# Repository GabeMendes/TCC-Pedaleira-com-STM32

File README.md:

# TCC-Pedaleira-com-STM32
Desenvolvimento de Unidade de Efeitos de áudio (Pedaleira) para Guitarra destinado ao Estudo de Processamento Digital de Sinais.

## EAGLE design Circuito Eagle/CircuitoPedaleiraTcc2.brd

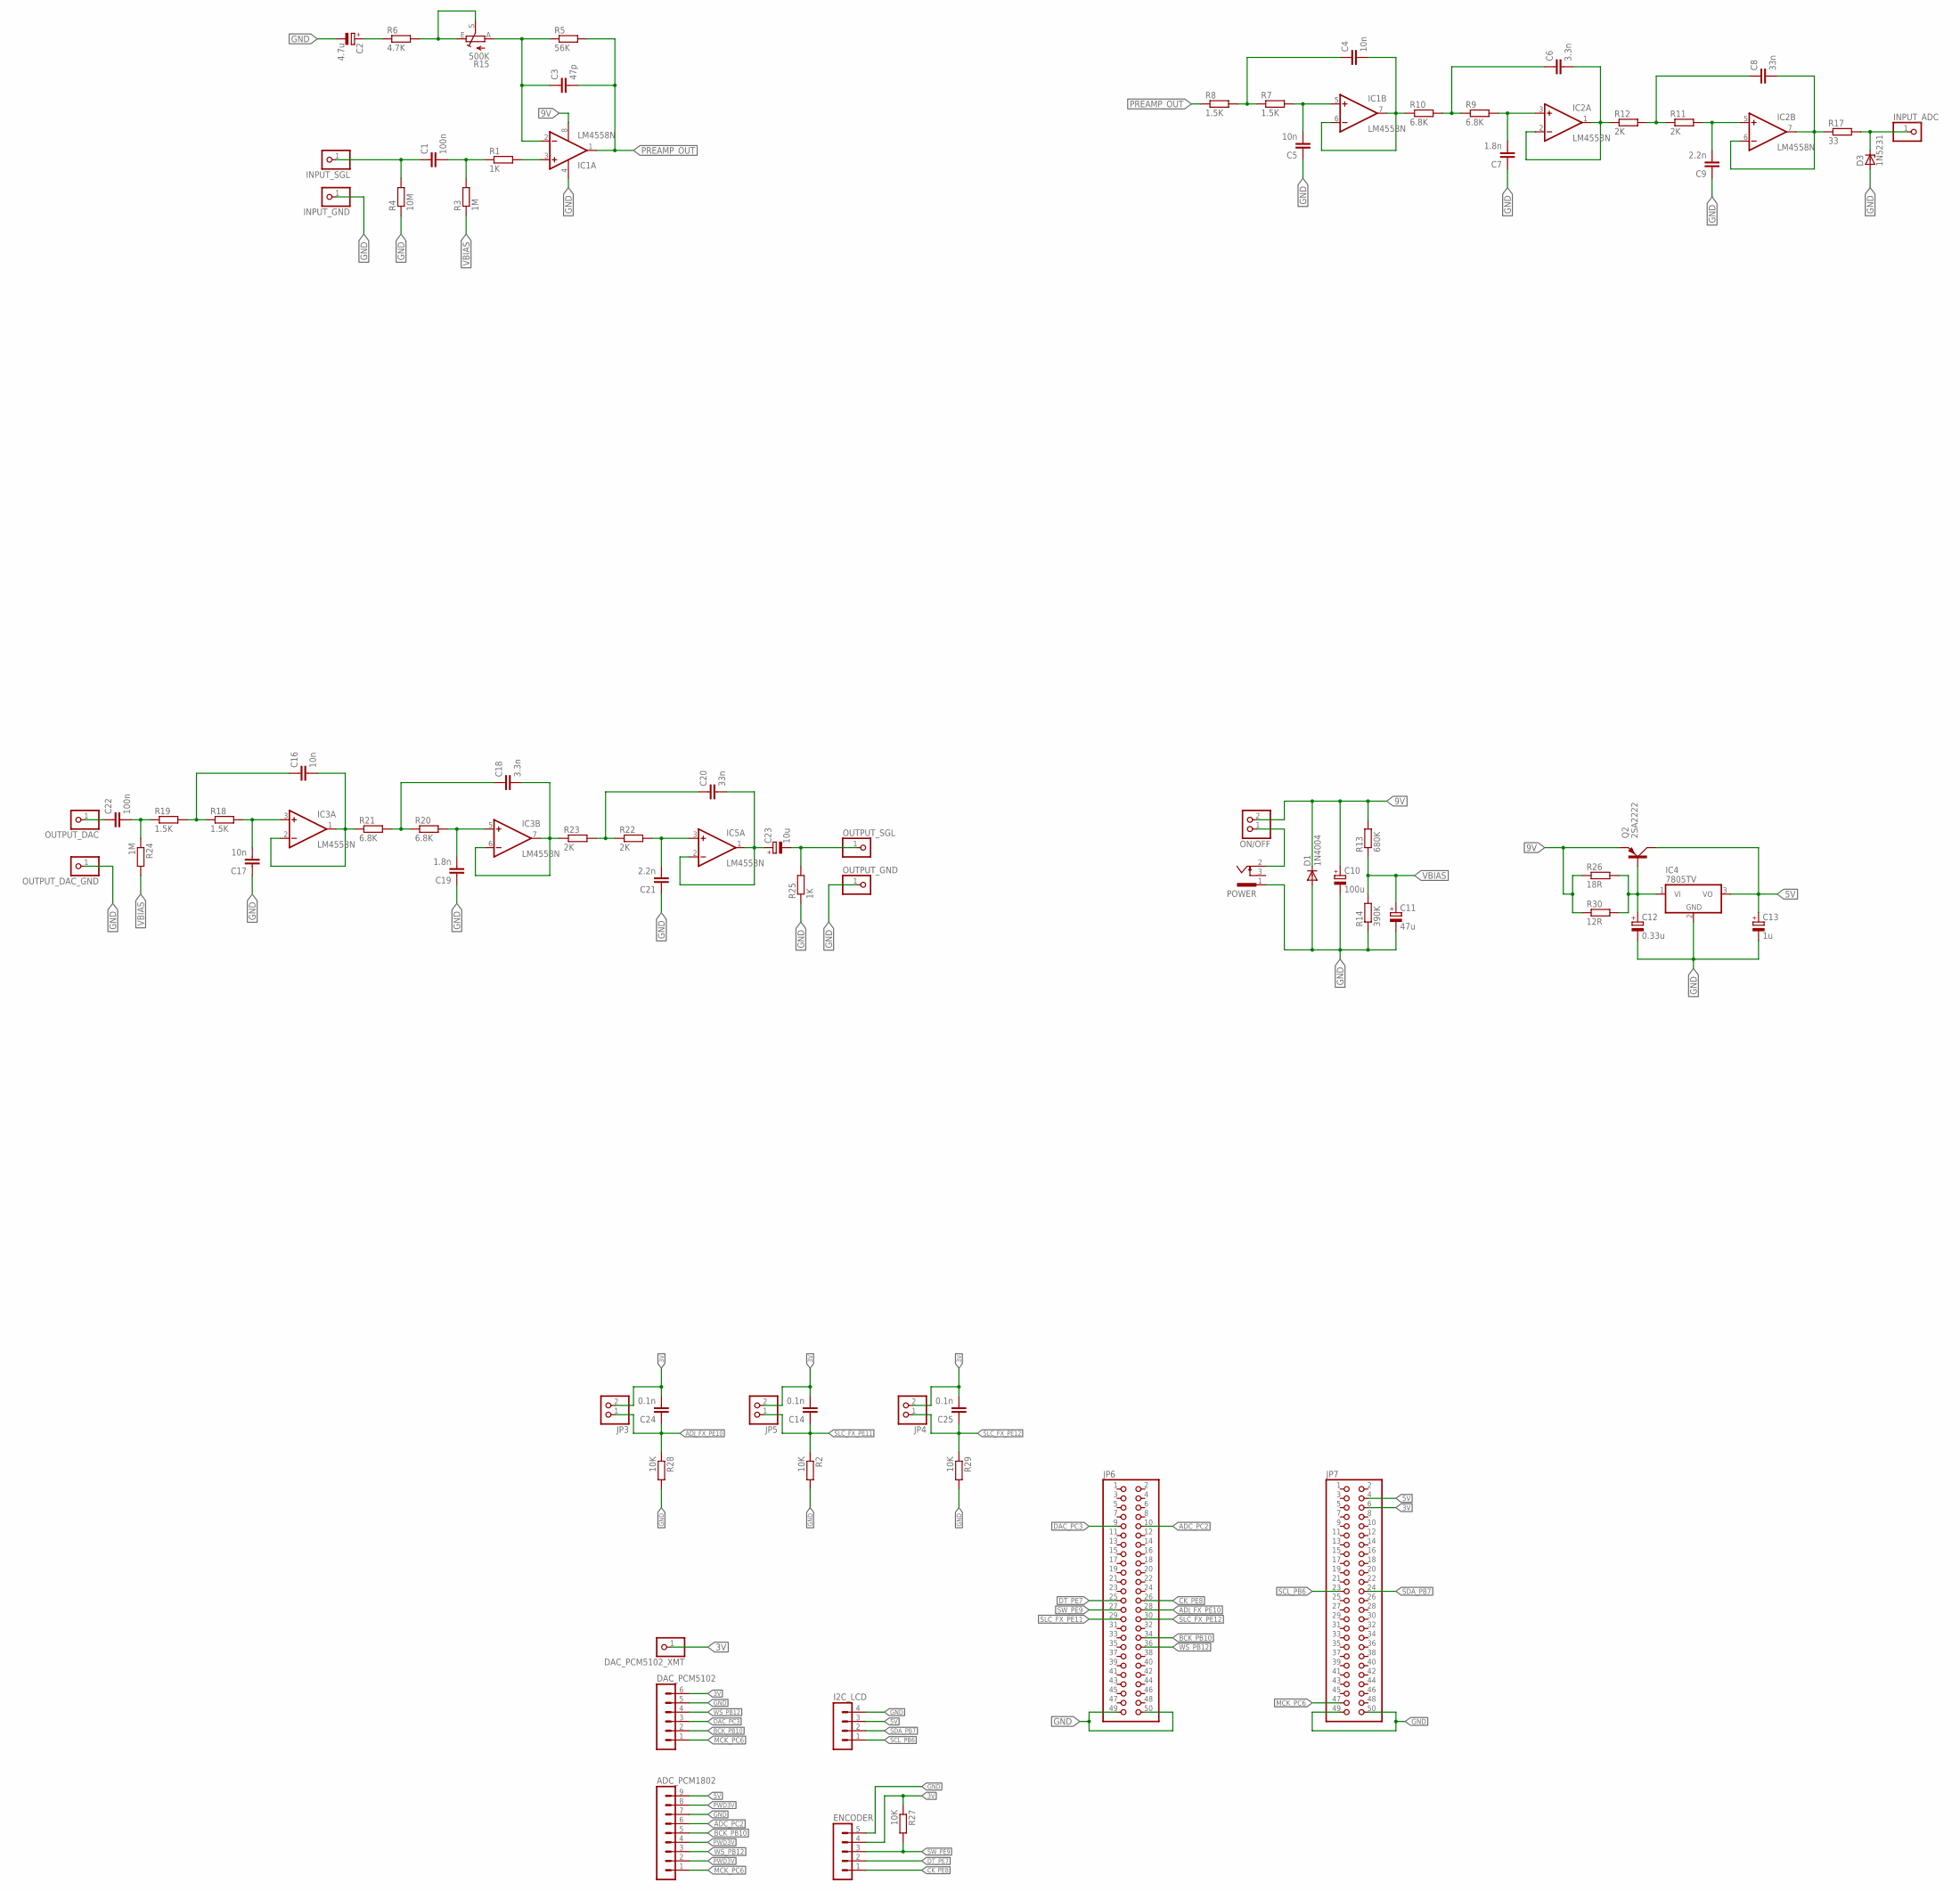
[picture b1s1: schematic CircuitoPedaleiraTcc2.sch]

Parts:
ADC_PCM1802: MA09-1
C1, C22: 100n; C025-025X050
C2: 4.7u; E2,5-6
C3: 47p; C025-025X050
C4, C5, C16, C17: 10n; C025-025X050
C6, C18: 3.3n; C025-025X050
C7, C19: 1.8n; C025-025X050
C8, C20: 33n; C025-025X050
C9, C21: 2.2n; C025-025X050
C10: 100u; E2,5-6
C11: 47u; E2,5-6
C12: 0.33u; E2,5-6
C13: 1u; E2,5-6
C14, C24, C25: 0.1n; C025-025X050
C23: 10u; E2,5-6
D1: 1N4004; DO41-10
D3: 1N5231; DO35Z10
DAC_PCM5102: MA06-1
DAC_PCM5102_XMT: PINHD-1X1; 1X01
ENCODER: MA05-1
I2C_LCD: MA04-1
IC1, IC2, IC3, IC5: LM4558N; DIL08
IC4: 7805TV; TO220V
INPUT_ADC: PINHD-1X1; 1X01
INPUT_GND: PINHD-1X1; 1X01
INPUT_SGL: PINHD-1X1; 1X01
JP3, JP4, JP5: PINHD-1X2; 1X02
JP6, JP7: PINHD-2X25; 2X25
ON/OFF: PINHD-1X2; 1X02
OUTPUT_DAC: PINHD-1X1; 1X01
OUTPUT_DAC_GND: PINHD-1X1; 1X01
OUTPUT_GND: PINHD-1X1; 1X01
OUTPUT_SGL: PINHD-1X1; 1X01
POWER: SCD-014A; SCD-014-A
Q2: 2SA2222; TO220AV
R1, R25: 1K; 0204/7
R2, R27, R28, R29: 10K; 0204/7
R3, R24: 1M; 0204/7
R4: 10M; 0204/7
R5: 56K; 0204/7
R6: 4.7K; 0204/7
R7, R8, R18, R19: 1.5K; 0204/7
R9, R10, R20, R21: 6.8K; 0204/7
R11, R12, R22, R23: 2K; 0204/7
R13: 680K; 0204/7
R14: 390K; 0204/7
R15: 500K; B25X
R17: 33; 0204/7
R26: 18R; 0411/15
R30: 12R; 0411/15

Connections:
3V: C14.2, C24.2, C25.2, DAC_PCM5102.6, DAC_PCM5102_XMT.1, ENCODER.4, JP3.2, JP4.2, JP5.2, JP7.6, R27.1
5V: ADC_PCM1802.9, C13.+, I2C_LCD.3, IC4.3 (VO), JP7.4, Q2.C
9V: C10.+, D1.C, IC1.8 (V+), ON/OFF.2, Q2.E, R13.2, R26.1, R30.1
ADC_PC2: ADC_PCM1802.6, JP6.10
ADJ_FX_PE10: C24.1, JP3.1, JP6.28, R28.1
AL_LP_OUT: C8.2, IC2.6 (-IN), IC2.7 (OUT), R17.1
AL_LP_OUT1: C20.2, C23.+, IC5.1 (OUT), IC5.2 (-IN)
BCK_PB10: ADC_PCM1802.5, DAC_PCM5102.2, JP6.34
CK_PE8: ENCODER.1, JP6.26
DAC_PC3: DAC_PCM5102.3, JP6.9
DT_PE7: ENCODER.2, JP6.25
GND: ADC_PCM1802.7, C2.-, C5.1, C7.1, C9.1, C10.-, C11.-, C12.-, C13.-, C17.1, C19.1, C21.1, D1.A, D3.A, DAC_PCM5102.5, ENCODER.5, I2C_LCD.4, IC1.4 (V-), IC4.2 (GND), INPUT_GND.1, JP6.49, JP6.50, JP7.49, JP7.50, OUTPUT_DAC_GND.1, OUTPUT_GND.1, POWER.1, R2.2, R4.1, R14.1, R25.1, R28.2, R29.2
INPUT: C1.1, INPUT_SGL.1, R4.2
INPUT_ADC: D3.C, INPUT_ADC.1, R17.2
MCK_PC6: ADC_PCM1802.1, DAC_PCM5102.1, JP7.47
unnamed: IC1.3 (+IN), R1.2
unnamed: C1.2, R1.1, R3.2
unnamed: ON/OFF.1, POWER.2
unnamed: C3.1, IC1.2 (-IN), R5.1, R15.A
unnamed: C4.2, IC1.6 (-IN), IC1.7 (OUT), R10.1
unnamed: R6.2, R15.E, R15.S
unnamed: C2.+, R6.1
unnamed: C16.2, IC3.1 (OUT), IC3.2 (-IN), R21.1
unnamed: C5.2, IC1.5 (+IN), R7.2
unnamed: C4.1, R7.1, R8.2
unnamed: C6.2, IC2.1 (OUT), IC2.2 (-IN), R12.1
unnamed: C7.2, IC2.3 (+IN), R9.2
unnamed: C6.1, R9.1, R10.2
unnamed: C9.2, IC2.5 (+IN), R11.2
unnamed: C8.1, R11.1, R12.2
unnamed: C17.2, IC3.3 (+IN), R18.2
unnamed: C16.1, R18.1, R19.2
unnamed: C18.2, IC3.6 (-IN), IC3.7 (OUT), R23.1
unnamed: C19.2, IC3.5 (+IN), R20.2
unnamed: C18.1, R20.1, R21.2
unnamed: C21.2, IC5.3 (+IN), R22.2
unnamed: C20.1, R22.1, R23.2
unnamed: C22.2, R19.1, R24.1
unnamed: C22.1, OUTPUT_DAC.1
unnamed: C12.+, IC4.1 (VI), Q2.B, R26.2, R30.2
OUTPUT: C23.-, OUTPUT_SGL.1, R25.2
PREAMP_OUT: C3.2, IC1.1 (OUT), R5.2, R8.1
PWD3V: ADC_PCM1802.2, ADC_PCM1802.4, ADC_PCM1802.8
SCL_PB6: I2C_LCD.1, JP7.23
SDA_PB7: I2C_LCD.2, JP7.24
SLC_FX_PE11: C14.1, JP5.1, JP6.29, R2.1
SLC_FX_PE12: C25.1, JP4.1, JP6.30, R29.1
SW_PE9: ENCODER.3, JP6.27, R27.2
V+: IC2.8 (V+), IC3.8 (V+), IC5.8 (V+)
V-: IC2.4 (V-), IC3.4 (V-), IC5.4 (V-)
VBIAS: C11.+, R3.1, R13.1, R14.2, R24.2
WS_PB12: ADC_PCM1802.3, DAC_PCM5102.4, JP6.36

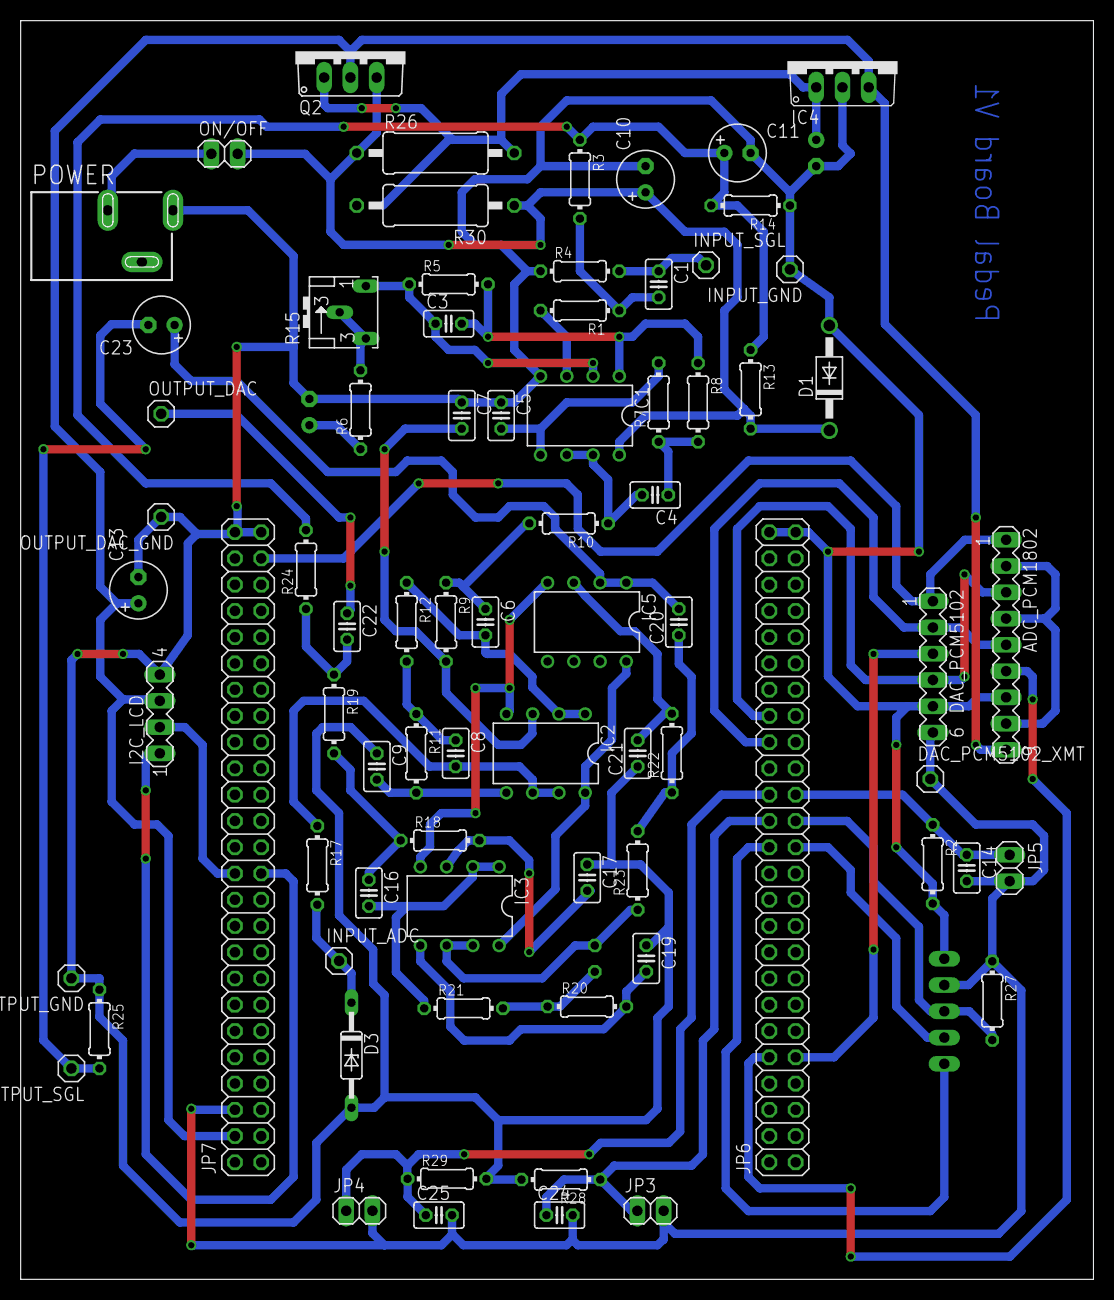
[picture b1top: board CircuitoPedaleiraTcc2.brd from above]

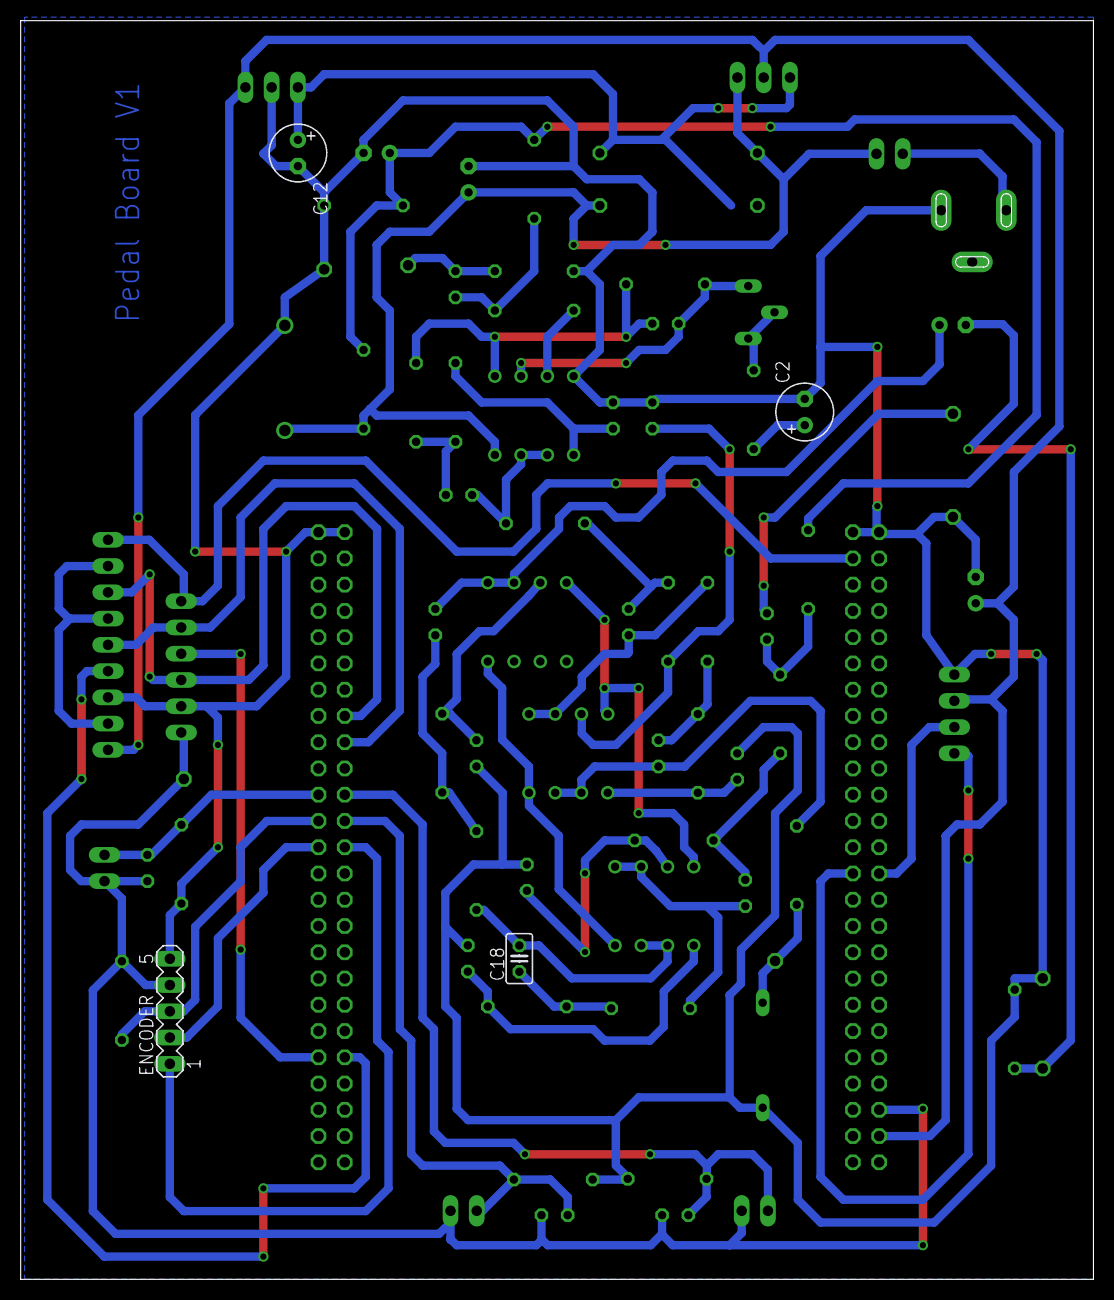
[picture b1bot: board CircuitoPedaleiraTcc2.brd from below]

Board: 2 copper layers, 103.8 x 121.8 mm, 80 parts (4 on the bottom side), 52 nets.

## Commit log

2023-12-26 Delete 0 - Pedal Clean.wav
    upload errado
2023-12-26 Delete 1 - Pedal Distortion.wav
    upload errado
2023-12-26 Delete 2 - Pedal Delay.wav
    upload errado
2023-12-26 Delete 3 - Pedal Tremolo.wav
    upload errado
2023-12-26 Delete 4 - Pedal Flanger.wav
    upload errado
